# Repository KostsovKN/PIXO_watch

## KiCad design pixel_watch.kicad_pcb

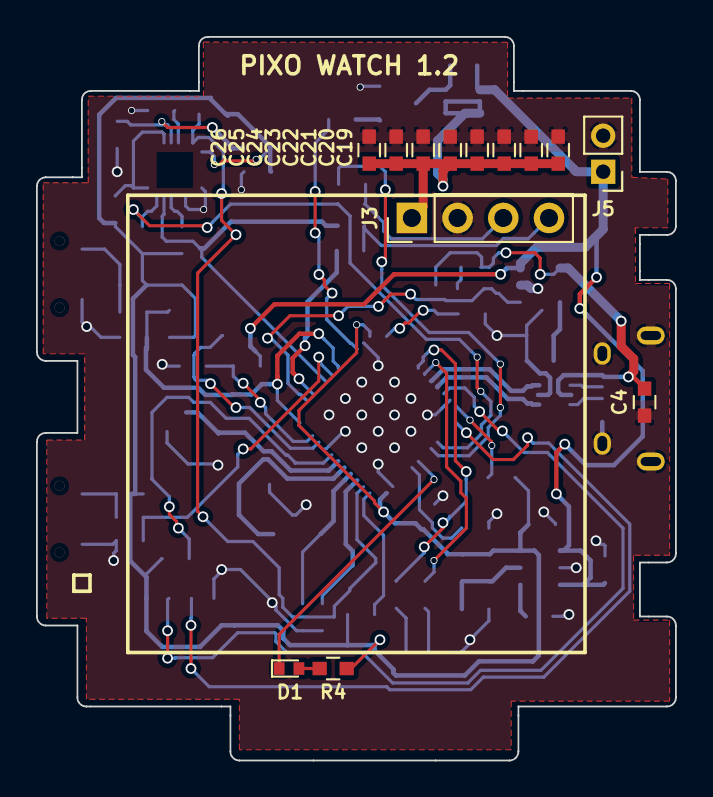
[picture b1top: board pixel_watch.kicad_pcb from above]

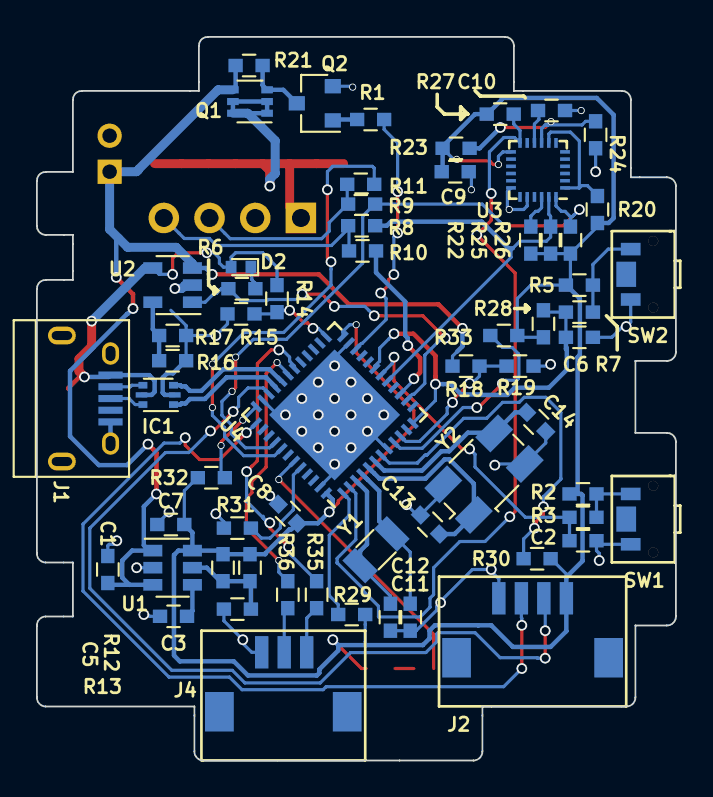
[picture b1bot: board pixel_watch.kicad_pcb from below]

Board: 2 copper layers, 35.5 x 40.2 mm, 75 parts (62 on the bottom side), 51 nets.

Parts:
C1, C7, C19, C20, C21, C22, C23, C24, C25, C26: 10uF; C_0603
C2, C4, C6, C8, C9, C10: 0.1uF; C_0603
C3: 0.01uF; C_0603
C5: 15pF; C_0603
C11, C12: 12.5pF; C_0603
C13, C14: 18pF; C_0603
D1, D2: LED; LED_0402
IC1: USBULC6-2P6; SOT-666
J1: USB_OTG; USB_Micro-B
J2: CONN_01X04; DF13A-4P-1.25H
J3: CONN_01X04; Pin_Header_Straight_1x04_Pitch2.54mm
J4: CONN_01X03; DF13A-3P-1.25H(20)
J5: CONN_01X02; Pin_Header_Straight_1x02_Pitch2.00mm
Q1: Q_PMOS_GDS; SC-70-6-P-CH
Q2: Q_NPN_BEC; SOT-23
R1, R2, R5, R8, R9, R10, R11, R15, R17, R18, R19, R21, R22, R23, R27, R28, R29, R30, R31: 10K; R_0603
R3, R7, R35, R36: 1K; R_0603
R4, R6: 470R; R_0603
R12: 44.2K; R_0603
R13: 30.1K; R_0603
R14: 19.1K; R_0603
R16: 2.5K; R_0603
R20, R24, R32, R33: 0R; R_0603
R25, R26: 4.7K; R_0603
SW1, SW2: SW_Push; P17065CT-ND
U1: TPS79301; SOT-23-6
U2: MPC73831; SOT-23-5
U3: MPU-9250; MPU9250
U4: STM32L452C(C-E)Ux_u; QFN-48-1EP_7x7mm_Pitch0.5mm
Y1: 32.768 KHz; Crystal_SMD_3215-2pin_3.2x1.5mm
Y2: 8.0MHz; Crystal_SMD_Abracon_ABM3B-4pin_5.0x3.2mm

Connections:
+3V3: C5.1, C7.1, C8.1, C9.1, J2.1, R2.1, R4.2, R5.1, R12.1, R20.1, R22.1, R23.1, R25.1, R26.1, R27.1, R28.1, R29.2, R30.2, R32.2, R33.2, U1.6, U3.13, U4.24, U4.48
+5V: C4.1, D2.2, IC1.5, J1.1, R14.1, U2.4
+BATT: C1.1, J5.1, Q1.3, R18.1, R21.1, U1.1, U1.3, U2.3
/Sheet5BA0C1D9/BATT_CHRG_STAT: R6.1, U2.1, U4.14
/Sheet5BA0C1D9/BATT_VOLT_SENSE: R18.2, R19.1, U4.10
/Sheet5BA0C1D9/Button_LB: C6.1, R7.1, R28.2, U4.12, U4.19
/Sheet5BA0C1D9/Button_LT: C2.1, R3.1, U4.18
/Sheet5BA0C1D9/DEBUG_LED: D1.1, U4.43
/Sheet5BA0C1D9/I2C3_SCL: R8.1, R25.2, U3.23, U4.17
/Sheet5BA0C1D9/I2C3_SDA: R9.1, R26.2, U3.24, U4.40
/Sheet5BA0C1D9/IMU_INT: R27.2, U3.12, U4.2
/Sheet5BA0C1D9/SPI1_MOSI: R11.1, U4.41
/Sheet5BA0C1D9/SPI1_SCK: R10.1, U4.15
/Sheet5BA0C1D9/SWCLK: J2.3, U4.37
/Sheet5BA0C1D9/SWDIO: J2.2, U4.34
/Sheet5BA0C1D9/USART1_RX: R36.2, U4.31
/Sheet5BA0C1D9/USART1_TX: R35.2, U4.30
/Sheet5BA0C1D9/USBD+: IC1.6, J1.3
/Sheet5BA0C1D9/USBD-: IC1.4, J1.2
/Sheet5BA0C1D9/USB_D+: IC1.1, U4.33
/Sheet5BA0C1D9/USB_D-: IC1.3, U4.32
/Sheet5BA0C1D9/USB_DETECT_INPUT: R14.2, R15.1, U4.25
/pixel_watch_top/CLK_sh: J3.4, R8.2, R10.2
/pixel_watch_top/MOSI_sh: J3.3, R9.2, R11.2
/pixel_watch_top/RGB_EN_TOP_sh: R1.1, U4.22
/pixel_watch_top/VCC_TOP: C19.1, C20.1, C21.1, C22.1, C23.1, C24.1, C25.1, C26.1, J3.1, Q1.2
GND: C1.2, C2.2, C3.2, C4.2, C6.2, C7.2, C8.2, C9.2, C10.1, C11.2, C12.2, C13.2, C14.2, C19.2, C20.2, C21.2, C22.2, C23.2, C24.2, C25.2, C26.2, IC1.2, J1.5, J1.6, J2.4, J3.2, J4.3, J5.2, Q2.2, R13.2, R15.2, R16.2, R17.2, R19.2, R24.2, R31.1, SW1.1, SW2.1, U1.2, U2.2, U3.18, U3.20, U4.8, U4.23, U4.35, U4.47, U4.49, Y2.2, Y2.4
unnamed: C3.1, U1.4
unnamed: C5.2, R12.2, R13.1, U1.5
unnamed: C10.2, U3.10
unnamed: C11.1, U4.3, Y1.2
unnamed: C12.1, U4.4, Y1.1
unnamed: C13.1, U4.5, Y2.1
unnamed: C14.1, U4.6, Y2.3
unnamed: D1.2, R4.1
unnamed: D2.1, R6.2
unnamed: J4.1, R35.1
unnamed: J4.2, R36.1
unnamed: Q1.1, Q2.3, R21.2
unnamed: Q2.1, R1.2
unnamed: R2.2, R3.2, SW1.2
unnamed: R5.2, R7.2, SW2.2
unnamed: R16.1, R17.1, U2.5
unnamed: R20.2, U3.1, U3.8
unnamed: R22.2, U3.22
unnamed: R23.2, R24.1, U3.9
unnamed: R29.1, U4.1
unnamed: R30.1, U4.7
unnamed: R31.2, U4.44
unnamed: R32.1, U4.36
unnamed: R33.1, U4.9

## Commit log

2018-10-14 Added very basic firmware for PIXO_watch harware
2018-10-14 Reconfigured directories
2019-10-27 Create CAD
